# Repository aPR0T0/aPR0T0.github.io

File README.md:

# apr0t0.github.io

A minimal, terminal-driven personal site for **Mohd Alqama Shaikh** — robotics &
embedded systems engineer.

Text-based, squared, monospace. Visitors can navigate either way:

- **Click** the GUI nav / links, or
- **Type** commands in the terminal: `./about`, `./resume`, `./projects`, `./projects/rdog`,
  `./blogs`, `./blogs/<slug>`, `./publications`, `./contact`, plus `ls`, `help`,
  `theme`, `whoami`, `clear`.

There's also a hidden **mascot**: type `traxx` (or `./angry-dario`, or any
[PetDex](https://petdex.dev) pet like `./boba` / `petdex random`) to summon an
interactive character that roams the page — see [Mascots](#mascots-interactive-characters).

## Stack

Pure static — no production build step or package installation. The portfolio
uses classic scripts and also works from disk. Beam Lab uses ES modules and
browser storage, so serve that section over HTTP or HTTPS.

```
index.html    structure + styles (squary terminal shell, light/dark)
posts.js      blog posts data (window.BLOG_POSTS) — rewritten by the editor
content.js    page content: bio, projects, publications, contact
app.js        terminal engine + hash router + commands
author.js     password-gated blog editor (WebCrypto + GitHub commit)
traxx.js      interactive mascot engine (pluggable characters)
characters/   one folder per mascot: character.js config + .svg frames
petdex.js     local PetDex pet provider (reads window.PETS)
pets/         vendored PetDex spritesheets + generated manifest.js
scripts/      fetch-pets.mjs — download/refresh vendored pets
media/        curated project images
sem/          SEM project plan and current design map
sem/lab/      published Beam Lab simulator, guides, and local-edition download
Phased-arrays/ Phased Array Bench (self-contained page, vendored three.js r128)
vla/          VLA pipeline blog in 3D (self-contained page, vendored three.js r128)
```

## Phased Array Bench

[Phased Array Bench](https://apr0t0.github.io/Phased-arrays/) is where I visualize phased arrays and study how they work: an interactive AESA model with beam-pattern scopes, a 3D radiation pattern, an exploded 3D model of the antenna tile, a link budget, and a dependency graph. It is one self-contained page in the site theme (shared light/dark choice). three.js r128 and OrbitControls are vendored in `Phased-arrays/vendor/` so the 3D views don't depend on a CDN. The [blog post](https://apr0t0.github.io/#blogs/phased-arrays) links to it, and `node scripts/check-phased-arrays.mjs` checks the page, vendored hashes and links before deploy.

## VLA pipeline in 3D

[Vision-Language-Action models, end to end](https://apr0t0.github.io/vla/) is a long-form post on how a robot foundation model gets made (the π0 / OpenVLA / GR00T-style recipe). The article scrolls along a vertical line of eight stages while a sticky 3D view shows each one: the pipeline graph, VLM pretraining, ALOHA-style teleop data collection, an action expert doing flow matching, towel-fold post-training, parallel RL environments, sim vs. real evaluation, edge quantization, and a bimanual robot running the policy in its control loop. Pointing at a stage previews its scene and clicking jumps to it. `?scene=N&t=S` opens one scene frozen at time `S`.

Everything is procedural three.js (r128 + OrbitControls, vendored in `vla/vendor/`), drawn in the site palette with the shared light/dark choice. `engine.js` is the 3D kit (materials, arms with IK, labels), `robots.js` holds the rigs and scripted tasks, `scenes-*.js` are the nine scenes and `page.js` is the scroll / hover runtime. The [blog entry](https://apr0t0.github.io/#blogs/vla) links to it, and `node scripts/check-vla.mjs` checks the page, vendored hashes, scenes and links before deploy.

## microchooser

[microchooser](https://apr0t0.github.io/microchooser/) picks the cheapest, easiest microcontroller or dev board for the peripherals you need, with buy links and KiCad symbols and footprints. It is built and deployed from its own repository, [aPR0T0/microchooser](https://github.com/aPR0T0/microchooser), which GitHub Pages serves at `/microchooser/`. This site links to it from the navigation and the projects page, using absolute URLs so the local link checks don't look for a `microchooser/` folder here.

## Agent Remote

[Open Agent Remote](https://apr0t0.github.io/remote/) is a permanent start page for a private OpenCode/Codex workspace. It remembers a Tailscale relay address in the visitor's browser and opens that private relay directly. Authentication and agent traffic stay on the relay laptop.

The page also provides a clean Windows/macOS/Linux laptop kit with launchers and a local setup GUI. Viewing devices need Tailscale and a supported browser; laptops hosting agents also run the connector. The public files contain no personal relay key, pairing, provider login, or conversation data.

The [Agent Remote release post](https://apr0t0.github.io/#blogs/agent-remote-private-ai-workspace) uses the portfolio's normal blog layout and provides direct downloads:

- Android: [`remote/agent-remote-latest.apk`](https://apr0t0.github.io/remote/agent-remote-latest.apk)
- Laptop kit: [`remote/agent-remote-laptop.zip`](https://apr0t0.github.io/remote/agent-remote-laptop.zip)

Both stable links are updated together. `remote/release.json` records their matching version and hashes, and `remote/checksums.txt` includes both files. The post explains paused transfers, native Codex visibility, and the need to update every laptop connector.

Refresh from the Agent Remote source project:

```bash
npm run apk
npm run build:pages
npm run stage:pages -- /path/to/apr0t0.github.io
```

Run `node scripts/check-remote.mjs` in this repository before publishing. It checks the public asset hashes, download checksum, archive paths, launcher permissions, and navigation link.

## Run locally

Just open `index.html` in a browser — it works offline via `file://`.

Or serve it (nicer hash-route behavior):

```bash
python3 -m http.server 8000
# open http://localhost:8000
```

Hash routes are shareable (e.g. `#projects/rdog`). Deploys to GitHub Pages via
`.github/workflows/deploy.yml`, which checks simulator assets and blog links
before publishing the repo root.

## Beam Lab and build journal

- [Launch Beam Lab](https://apr0t0.github.io/sem/lab/)
- [Read the project journal](https://apr0t0.github.io/#blogs/building-a-simple-electron-microscope)
- [SEM project plan](https://apr0t0.github.io/sem/)

The hosted simulator runs entirely in the visitor's browser. BOM edits and
named setups stay in that browser's storage; they never rewrite this repository.
Component research needs the localhost edition and the visitor's own Codex
session. A curated, self-contained local source ZIP is linked from
`sem/lab/run-locally.html`; it requires no access to the private development repo.

The 512 × 512 butterfly preset uses 140 µm field width and about 109 minutes of
modeled hardware acquisition. The 500× preview takes about 13 seconds. Images
are synthetic; the electronics are unbuilt reference designs.

Refresh the hosted copy from the Beam Lab source checkout:

```sh
node /path/to/simplest-electron-microscope/simulator/build-static.mjs \
  --out /path/to/portfolio/sem/lab \
  --base-path /sem/lab/ \
  --blog-url '/#blogs/building-a-simple-electron-microscope'
node scripts/check-sem.mjs
```

The publisher uses an explicit asset list, records SHA-256 hashes, preserves
the base version, and omits personal run history, credentials, and development
data. Commit the refreshed `sem/lab/` files alongside any journal changes;
the Pages workflow does not need private-repository credentials.

## Editing content

Page content lives in `content.js`: bio, projects, publications, and contact
channels. Add a project by appending to the `projects` array; drop images into
`media/<id>/` and reference them in that project's `media` list. Blog posts live
in `posts.js` (`window.BLOG_POSTS`).

The `./resume` page is the `resume` object in `content.js`; its bullets are
inline markdown, so they can link to `#projects/<id>` / `#blogs/<slug>`. The
downloadable copy is `media/resume/alqama-shaikh-resume.pdf` — replace that file
when the resume changes.

## Mascots (interactive characters)

Type a character's name in the terminal to summon a little companion. It pops
out of the terminal, roams the screen, turns to watch the prompt while you type,
and panics when you pick it up and drag it anywhere.

```
traxx            summon / hide DJ TRAXX (the default)
traxx <name>     summon a specific character   (e.g. traxx angry-dario)
./<name>         same, in the site's ./ style  (e.g. ./angry-dario)
traxx list       list registered characters
traxx bye        send the current one away     (Esc or the × button work too)
```

`angry-dario` ships as a second, ready-to-copy example.

### PetDex pets (vendored locally)

`petdex.js` connects the same engine to pets from [PetDex](https://petdex.dev),
the gallery of animated Codex pets. Pets are **vendored into this repo** (their
spritesheets live under `pets/`), so they load from the site's own origin — no
runtime calls to petdex.dev. That makes them **blocker-proof, offline-proof, and
`file://`-friendly** (an earlier CDN-streaming version showed only a placeholder
when an ad/tracking blocker blocked the CDN — this fixes that for good).

```
./<slug>              summon an INSTALLED pet   (local, instant, offline)
<slug>                same, without the ./
spawn <name>          fetch ANY petdex pet by name over the network, then show it
petdex list           list installed pets
petdex find <query>   search installed pets
petdex random         summon a random installed pet
petdex state <id>     play any expression on the current pet (see below)
petdex seats on|off   perch the current pet on every nav / toolbar button
petdex bye            send it away              (Esc / × also work)
```

`./<slug>` only loads pets that are **vendored** in this repo (no network — works
offline / behind blockers). To bring in a pet that isn't installed yet, use
`spawn <name>`: it goes to petdex.dev, resolves the name, and loads the sprite on
demand (needs a connection, and won't work if petdex.dev is blocked). If you want
that pet to be permanent + offline, vendor it with the script below.

**Installing pets** — one command downloads them into `pets/` and regenerates
`pets/manifest.js`:

```bash
node scripts/fetch-pets.mjs boba dalek pixel-panda   # add pets by name/slug
node scripts/fetch-pets.mjs --curated                # add all official curated pets
node scripts/fetch-pets.mjs --remove homelander      # drop one
```

Names can be slugs, display names, or `petdex.dev/pets/<slug>` URLs. Browse the
gallery at [petdex.dev](https://petdex.dev) to find names. Commit the new files
in `pets/` and they deploy with the site. (Sheets are re-encoded for size; a full
sheet is ~0.5 MB.)

Each pet is one spritesheet whose rows are the **9 animation states**, all
reachable (`petdex state <id>`): `idle`, `running-right`, `running-left`,
`waving`, `jumping`, `failed`, `waiting`, `running`, `review`. The engine maps
them to behaviour automatically — it runs left/right while roaming, `review`s
while you type, and `failed`s (panics) when you grab it. Every so often the
roaming pet **walks over and hops onto a button**, sits *on top* of it, comments
on that option, then **hops from button to button** before dropping back down —
no command needed. You can also **drag the pet onto any button** to seat it there
yourself. All of this works for whichever character is out (`./boba`, `./nukey`,
`spawn <name>`, …), not just one.

`petdex seats on` perches a pet on **every nav / toolbar button**. They *rain in*
(each drops onto its button with a bounce), then keep it lively — every few
seconds a random one **falls onto its button again** or pops a little speech
bubble riffing on that option (e.g. on `./projects`: "ooh, robots!"; on the theme
button: "flip the lights!"). Hovering a button makes its pet **wave** and comment;
clicking makes it **jump**; the current page's pet sits in `review`. Use
`petdex seats <name>` to pick who sits, `petdex seats off` to clear. If a sheet is
ever missing, the pet shows a labelled placeholder instead of an invisible walker.

Pets are community fan art — code is MIT, assets belong to their submitters
([takedowns](https://github.com/crafter-station/petdex)).

### Add your own

A character is just a folder under `characters/` plus a one-line script tag — no
build step.

1. Create `characters/<id>/` and add SVG frames (any `viewBox`, drawn facing the
   viewer). Only `idle.svg` is required; the rest fall back to it:

   ```
   characters/my-bot/
     idle.svg     required — resting pose
     look.svg     optional — shown while you type
     panic.svg    optional — shown while held / dragged
   ```

2. Add `characters/my-bot/character.js`:

   ```js
   window.Traxx.define({
     id: "my-bot",
     name: "MY BOT",
     height: 140, aspect: 112/140, speed: 64,
     sign: { bg: "#111", fg: "#0af" },      // LED name-tag (or null to hide)
     states: {
       idle:  { frames: "idle",  anim: "bob-slow" },
       walk:  { frames: "idle",  anim: "bob" },
       look:  { frames: "look",  anim: "bob-slow", lean: true },
       panic: { frames: "panic", anim: "shake" },
     },
     speech: {
       hello: ["hi!"], panic: ["aaah!"], land: ["oof."], idle: ["..."],
     },
   });
   ```

3. Load it in `index.html`, after `traxx.js`:

   ```html
   <script src="./characters/my-bot/character.js"></script>
   ```

   Then run `./my-bot`.

**Notes**

- `frames` is an SVG name (without `.svg`), or a list to cycle for frame-by-frame
  animation — `{ frames: ["walk-a","walk-b"], fps: 8 }`.
- `anim` is a built-in motion — `bob-slow`, `bob`, `shake`, `none` — or a custom
  one you supply via a `css` field (see `characters/angry-dario` for a `stomp`
  example). `lean: true` makes the character tilt toward the prompt.
- Frames are plain `` loads, so mascots work offline over `file://` too.
- Respects `prefers-reduced-motion`, is touch-friendly, and only one mascot is
  out at a time.

## Author mode (in-browser blog editor)

Blog posts can be written/edited from the terminal and committed straight to the
repo — no backend. Your GitHub token is encrypted with a password using real
WebCrypto, so no secret is ever stored in plaintext.

**Crypto:** AES-256-GCM with a key derived via PBKDF2-SHA256 (600,000
iterations, random 16-byte salt + 12-byte IV). `login` decrypts the token with
your password; a wrong password fails AES-GCM auth-tag verification, so the
password *is* the key (no separate hash is kept).

**Commands:**

```
auth setup      encrypt a GitHub token with a password (one time)
login           unlock author mode with your password
edit <slug>     edit a post in an inline editor, then commit
new             write a new post, then commit
auth publish    store the encrypted blob in the repo (auth.json) for
                cross-device login — it stays ciphertext, never plaintext
auth status     show current auth state
auth reset      remove the encrypted blob from this browser
logout          lock author mode
```

Committing rewrites `posts.js` via the GitHub Contents API; GitHub Pages then
redeploys automatically (~1 min).

**Security notes**

- Use a **long passphrase**. The encrypted blob (in `localStorage`, or in
  `auth.json` if you publish it) is only as safe as your password is hard to
  brute-force.
- Use a **fine-grained personal access token** scoped to **only this repo** with
  **Contents: read & write** and an **expiry**. That caps the blast radius.
- Requires a secure context (https or localhost / `file://`) for WebCrypto.

## RK3566 circuit simulation lab

[Open the RK3566 lab](https://apr0t0.github.io/rk3566/) to explore the Revision 4
PCB, saved simulation runs, model studies, and electromagnetic field analysis.
The site navigation and `./projects/rk3566` also link to the lab.

The Pages package is a dated snapshot of the local analysis. Interactive views,
playback, saved-run selection, and evidence downloads work on Pages. New Python
solver runs and validation sweeps require the local simulation service.
`rk3566/publication.json` records the export time, source identities, API-to-file
mapping, and hashes of the exported evidence. See `scripts/export-rk3566.py` for
the repeatable data export and `rk3566/README.md` for the published UI behavior.

Validate with `node scripts/check-rk3566.mjs`; the Pages workflow runs this check
alongside the existing SEM and Agent Remote checks before deploying.

The [whole-board magnetic view](https://apr0t0.github.io/rk3566/#magnetic) adds
conditional contributions from the saved averaged power-rail currents across the
55 × 55 mm board. It supports height selection, B/H field values, source selection,
playback and probes; the same study is available in the 3D workbench. Each current
path and return is an explicit geometric assumption. Unsupported current paths
remain outside the modeled sum and are listed in its coverage report.

Generate its evidence with `python3 -B board_magnetic.py` from the local simulation
directory before running the Pages export. `node scripts/check-board-magnetic.mjs`
checks the published field data and its numerical contract.

## robot-learning node map

[robot-learning](https://apr0t0.github.io/robot-learning/) is the code that goes with the VLA post: a node-based pipeline where every stage has a working base and every paper is a swappable component, configured from YAML or Python. The page in `robot-learning/` is a node map of that repo (stages, components with their params and papers, pipeline DAGs, and the files that implement each one). It is generated in the robot-learning repo by `scripts/build_site.py` and copied here with its `scripts/publish_site.sh`; `node scripts/check-robot-learning.mjs` checks the page, its graph data and the links before deploy.

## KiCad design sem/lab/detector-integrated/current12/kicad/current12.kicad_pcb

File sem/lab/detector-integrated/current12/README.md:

# Specimen-current board · current12

Current12 · B0 · unbuilt. One DC input powers the existing LMC662 / ADS1115 measurement circuit. Connect the insulated conductive specimen holder to SUM. The amplifier common and chamber share one deliberate ground reference.

Input: 12 / 24 V · regulated 9–30 V. Local rails: ±5 V analog · 3.3 V ADC.

## Exact external connections

Connector pin numbers, not screen orientation, define the wiring. Pin 1 uses the marked / square pad in the native footprint. Match this revision before assembly.

| Pin | Net | External connection | Detail |
|---|---|---|---|
| J2.1 | VIN | DC source +12 V or +24 V | Use regulated 9–30 V; verify polarity before applying power. |
| J2.2 | PGND | DC source negative | Primary return; bonded to local analog ground on this board. |
| J1.1 | SUM | Insulated conductive specimen holder | Feedthrough centre only. No second ground connection to the specimen holder. |
| J1.2 | AGND | Input guard / shield | Grounded-reference guard. Keep the signal conductor insulated from it. |
| J3.1 | AGND | ESP32 GND | Reference for the direct I²C signals. |
| J3.2 | +3V3 | Leave open | ADC reference OUTPUT; do not feed or power an ESP32 through this pin. |
| J3.3 | SDA | ESP32 GPIO21 | 3.3 V I²C data. Both devices must be powered while connected; coordinate power or disconnect before separate power cycling. |
| J3.4 | SCL | ESP32 GPIO22 | 3.3 V I²C clock. |
| J3.5 | RDY | Leave open with the supplied polling sketch | Optional ADC conversion-ready output. |
| J4.1 | PGND | Chamber / enclosure ground star | Use a separate mechanically secure protective-earth bond for accessible metal; PCB wiring is not that bond. |
| J4.2 | PGND | Same ground star / shield return | Duplicate PGND terminal; internally connected to J4.1. |

## Design files

- Open `kicad/current12.kicad_pro` with KiCad 10. The complete design ZIP includes all hierarchical sheets and local libraries.
- `exports/schematic.pdf` contains every schematic sheet.
- `exports/assembly.svg` identifies the component positions.
- `bom.csv` contains the selected parts; prices are not quoted.
- `verification/check-summary.json` records native checks and checked-file hashes.
- `fabrication.zip` contains prototype manufacturing outputs. Inspection and bench commissioning remain required.

Use the original ESP32_LMC662_scan sketch and DAC80502 scan board. J3.2 is the ADC reference **output**, which remains open with that host. Read the separate scan-board connection guide.

---

## Shared architecture and commissioning

Two unbuilt PCB prototypes extend the original LMC662 / ADS1115 detector. Use the [interactive board and pin guide](https://apr0t0.github.io/sem/lab/power.html) to select specimen current or the positive collector. Both accept a regulated 9–30 V input, including nominal 12 V and 24 V. This supply powers detector electronics and collector bias; the electron gun, scan drivers and grounded ESP32 have separate supplies.

## What is onboard

Input fuse and reverse-polarity diode → LMR51420 500 kHz buck → approximately 5.09 V → RECOM R05P09D/P isolated raw ±9 V → RC filtering → TPS7A49 / TPS7A30 local ±5 V. The ADC runs from its own 3.3 V supply regulator. The collector also has a separate digital 3.3 V rail, an ATmega328P and two VO2611-X016 optocouplers.

The collector's XP Power CA02P-5 module is soldered onto the same board. It creates programmable 0–200 V from the onboard 5 V bus. Two 10 kΩ filter stages and 100 nF / 1 µF capacitors feed FCOM. Nominal FCOM at a raw 200 V is about 199.6 V because of bleeder loading. A TPS2553-1 latch-off switch limits the bias-module input: 88.7 kΩ / 1% programs a calculated 262–342 mA range, below the module’s 420 mA short-protection input limit. Its active-LOW fault goes through J3.7 to ESP32 GPIO34. Verify startup and current-limit behavior on the assembled board. Program linearity is specified from 15% of full scale, so treat low-bias settings as requiring calibration.

The isolated supply and HV converter are packaged modules; the buck is a discrete IC / inductor circuit. This is a self-contained onboard power design, not an entirely discrete magnetics design. Obtain current distributor quotes: the HV module may dominate cost.

Both layouts use local top/bottom PGND copper and six stitching vias around the buck's ground returns. The amplifier's C9/C10 bypass capacitors have direct 0.75 mm returns to the quiet AGND or FCOM plane. The guarded SUM trace and its no-plane region remain separate. These filled-copper connections were inspected in the native boards; their noise performance still requires measurement.

## Choose the current path

| Connection | Specimen-current board | Collector board |
|---|---|---|
| J1.1 SUM | Insulated conductive specimen holder | Separate insulated metal collector |
| J1.2 guard | AGND, near chamber ground | FCOM, near positive collector bias |
| Specimen | Only through SUM; insulated from stage | Grounded conductive contact |
| Local analog common | Deliberately bonded to PGND/chamber | Elevated FCOM |
| J3 data | Direct 3.3 V I²C to ESP32 | Ground-side UART through two optocouplers |
| Extra bias | None | Generated and filtered onboard |

The specimen-current board’s direct I²C is not isolated during power-off. Keep both host and detector powered while connected, using coordinated power; disconnect the interface before separately power-cycling either side. The collector uses host-powered VIO at J3.2 for its ground-side UART interface.

SUM is the amplifier input. The positive bias connects to FCOM, never directly to SUM; a direct bias wire would bypass the measurement. At steady state, unsaturated feedback holds SUM close to the amplifier's local common. The collector reading is net collected electron current, potentially a mixture of SE, BSE and background. There is no charge multiplication on a plain metal collector. An insulating specimen still needs a charging solution.

## Collector boundary

The complete analog circuit, ADS1115 and ATmega328P operate relative to FCOM. The primary side, CA converter case/return, outer enclosure, accessible cable shield, grounded specimen and scan ESP32 operate relative to chamber ground. Only the rated isolated converter, two optocouplers and deliberate filtered bias network bridge these references. No grounded USB, programming or oscilloscope cable belongs on FCOM while biased.

Mount the collector PCB on nylon / PEEK standoffs with insulating fasteners. Four 3.2 mm holes reserve a maximum 6.4 mm diameter insulating washer envelope. A grounded screw head is not an electrically neutral hole: maintain separation from grounded metal above and below the floating copper.

The PCB design enforces a 5 mm copper separation between primary and FCOM regions and a separate 2 mm rule between grounded-side HV and low-voltage conductors. These are layout rules, not certification. RECOM's 250 VAC rms basic working insulation is the relevant published working specification; 6.4 kV is a brief test rating. Converter and optocoupler capacitance still carries displacement current. Rail filters cannot remove every path for common-mode pickup.

## Collector startup and shutdown

1. Verify component orientations, cleanliness, connector numbering and the exact BOM. Assemble and inspect the input power stages before fitting the high-impedance parts where practical.
2. With the electron beam blanked and the HV module disabled, power from a current-limited regulated source. Verify 5 V bus, ±9 V raw rails, ±5 V local rails and both 3.3 V domains using their correct reference. Repeat at 12 V and 24 V and across expected loads.
3. Program the ATmega328P for an external 8 MHz crystal and 3.3 V operation with bias disabled and verified discharged. Remove all ICSP connections. Connect the grounded ESP32 via the specified UART, two control pins and active-LOW fault input. Feed collector J3.2 HOST_VIO from the ESP32’s 3.3 V rail (allow 19 mA); this removes the board-powered LED/pull-up injection path into host GPIO. Leakage and hot-plug behavior remain unverified. On the specimen-current board, J3.2 is instead a reference output and is left open.
4. Begin with the bias pot at minimum. The ESP32 first confirms the optical link. Its `b` command raises HV_ENABLE while holding PGM_RELEASE LOW for at least 100 ms, then releases the buffered RC ramp. Hardware also uses a TPS3808G50 to qualify the actual module 5 V rail, with a datasheet delay of 180–420 ms before allowing PGM_RELEASE to release the clamp. The buffer remains powered from the unswitched 5 V bus. A 10 kΩ / 47 µF command filter gives about 0.47–0.59 s nominal ramp time; effective capacitance and leakage must be checked. The sketch keeps the beam blanked for a 10 s initial settling policy and checks the optical link during that interval. That delay is a starting policy, not a guarantee of pA settling. Measure the actual bias rise, overshoot and settling before deciding the interval is adequate.
5. With bias steady and beam blanked, use `z` to measure a new zero. Only then use `s` for a scan. Repeat zero after any bias adjustment. The acquisition sequence requests fresh ADC conversions; CRC, request IDs, status and timeouts reject incomplete or stale replies.
6. `x` aborts, blanks the beam, clamps programming to zero and removes the CA module's 5 V input. Passive bleeders remain connected. Check voltage with a rated instrument before touching or attaching a programmer; a software OFF state is not proof of discharge.

The final 1 µF capacitor alone stores 20 mJ at 200 V. Its independent 9.98 MΩ bleeder has a 9.98 s time constant, but additional paths and unspecified module internal capacitance affect whole-assembly discharge. Measure the complete assembly, including cables and relevant faults. These software controls are not a certified beam interlock.

## Proving that readings are electrons

- Inject a known local current into SUM at zero bias and elevated bias. Establish gain, sign, offset, clipping and settling with the real cable and feedthrough.
- Log the collector dark current with pumps, heater, converters and UART operating. Repeat a raster with the beam blanked and then blocked upstream; image structure under those conditions is pickup.
- Compare repeated scans and measured incident beam current. Repeat at fixed, settled bias values. Separate bias-dependent leakage and displacement current from collection changes.
- Record raw ADC codes, zero, calibration, timing, measured bias and all faults. A clean DRC does not establish a picoampere noise floor.

The board-specific package contains the exact connector schedule, native CAD, BOM, CAD results and prototype fabrication outputs. The original externally powered Rev A and the earlier battery / fibre collector concept remain separate options on their original pages.

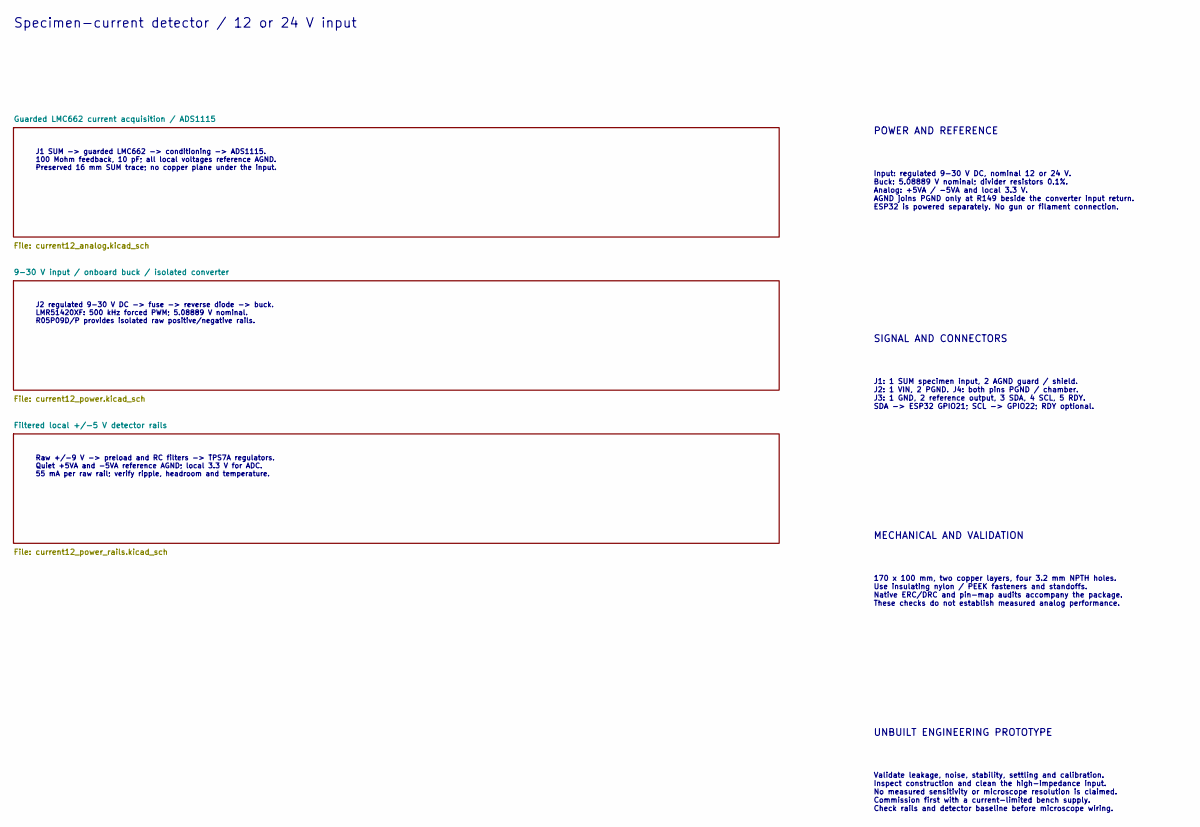
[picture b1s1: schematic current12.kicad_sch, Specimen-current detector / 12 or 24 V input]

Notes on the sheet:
Specimen-current detector / 12 or 24 V input
J1 SUM -> guarded LMC662 -> conditioning -> ADS1115. 100 Mohm feedback, 10 pF; all local voltages reference AGND. Preserved 16 mm SUM trace; no copper plane under the input.
J2 regulated 9-30 V DC -> fuse -> reverse diode -> buck. LMR51420XF: 500 kHz forced PWM; 5.08889 V nominal. R05P09D/P provides isolated raw positive/negative rails.
Raw +/-9 V -> preload and RC filters -> TPS7A regulators. Quiet +5VA and -5VA reference AGND; local 3.3 V for ADC. 55 mA per raw rail; verify ripple, headroom and temperature.
POWER AND REFERENCE
Input: regulated 9-30 V DC, nominal 12 or 24 V. Buck: 5.08889 V nominal; divider resistors 0.1%. Analog: +5VA / -5VA and local 3.3 V. AGND joins PGND only at R149 beside the converter input return. ESP32 is powered separately. No gun or filament connection.
SIGNAL AND CONNECTORS
J1: 1 SUM specimen input, 2 AGND guard / shield. J2: 1 VIN, 2 PGND. J4: both pins PGND / chamber. J3: 1 GND, 2 reference output, 3 SDA, 4 SCL, 5 RDY. SDA -> ESP32 GPIO21; SCL -> GPIO22; RDY optional.
MECHANICAL AND VALIDATION
170 x 100 mm, two copper layers, four 3.2 mm NPTH holes. Use insulating nylon / PEEK fasteners and standoffs. Native ERC/DRC and pin-map audits accompany the package. These checks do not establish measured analog performance.
UNBUILT ENGINEERING PROTOTYPE
Validate leakage, noise, stability, settling and calibration. Inspect construction and clean the high-impedance input. No measured sensitivity or microscope resolution is claimed. Commission first with a current-limited bench supply. Check rails and detector baseline before microscope wiring.

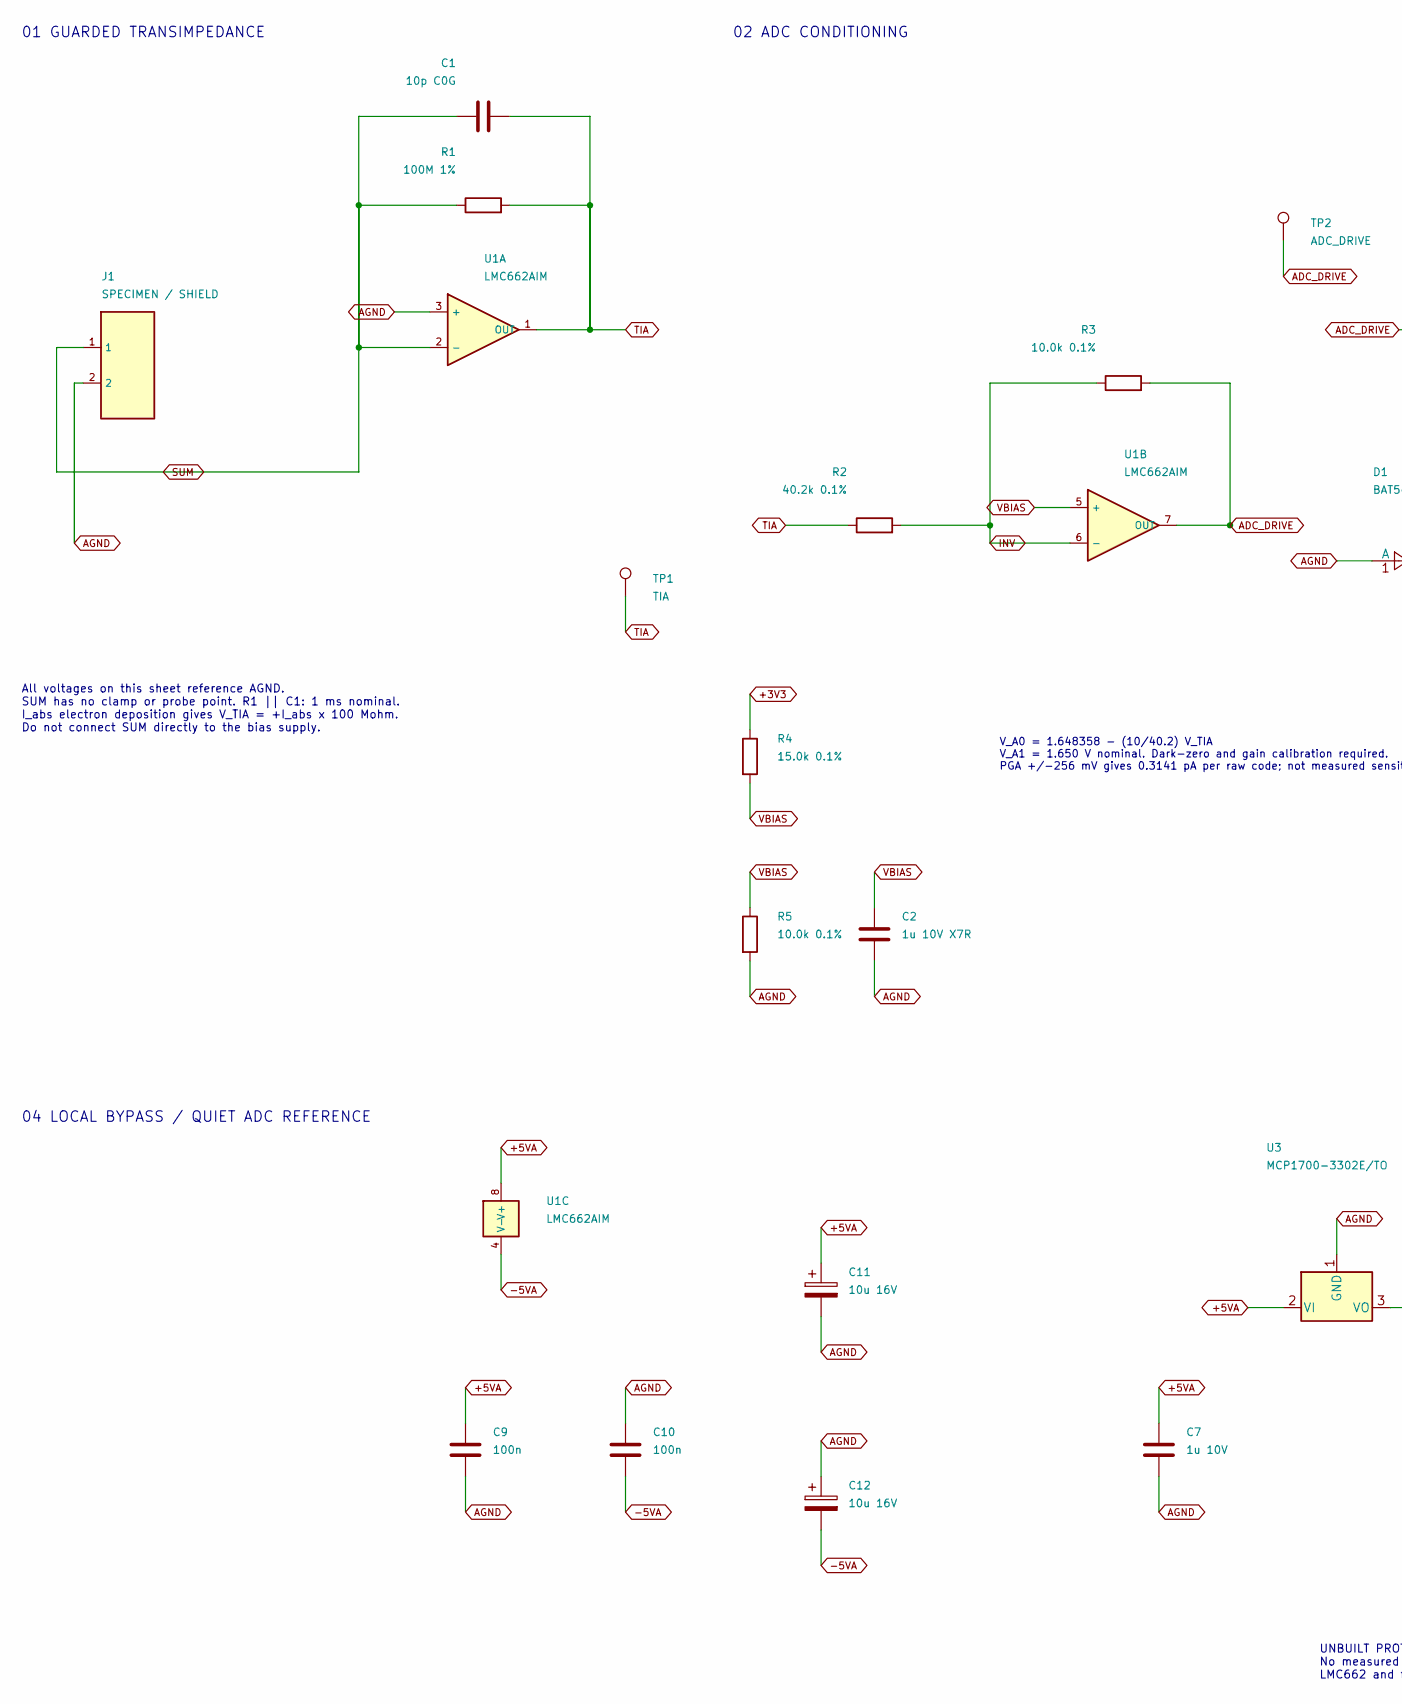
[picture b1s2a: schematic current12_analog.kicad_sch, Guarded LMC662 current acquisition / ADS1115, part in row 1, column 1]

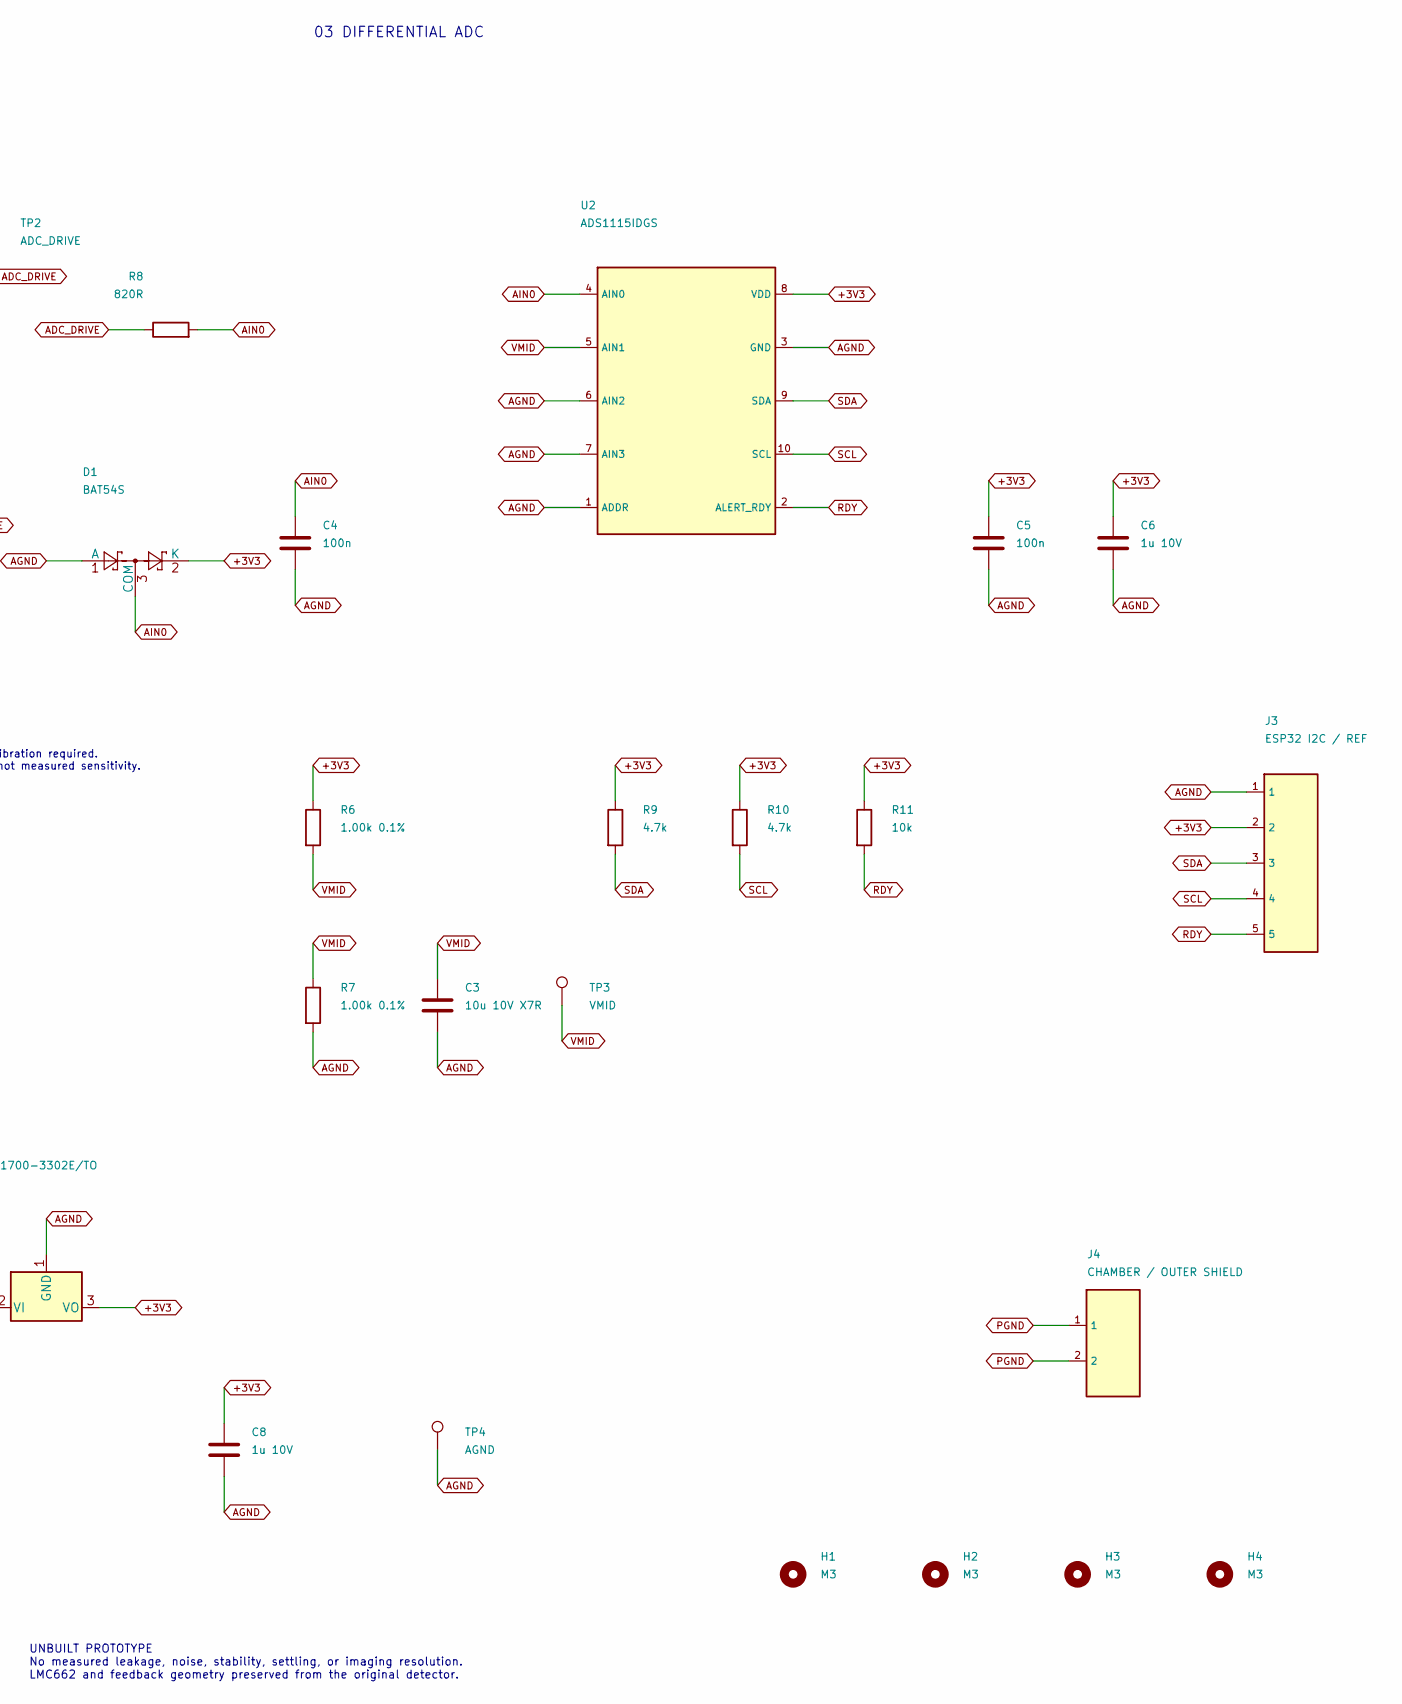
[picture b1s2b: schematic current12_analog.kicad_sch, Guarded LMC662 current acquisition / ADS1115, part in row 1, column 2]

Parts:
C1: 10p C0G; C_Disc_D3.0mm_W1.6mm_P2.50mm
C2: 1u 10V X7R; C_0805_2012Metric
C3: 10u 10V X7R; C_0805_2012Metric
C4, C5, C9, C10: 100n; C_0805_2012Metric
C6, C7, C8: 1u 10V; C_0805_2012Metric
C11, C12: 10u 16V; CP_Radial_D5.0mm_P2.00mm
D1: BAT54S; SOT-23; MPN BAT54S
H1, H2, H3, H4: M3; MountingHole_3.2mm_M3
J1: SPECIMEN / SHIELD; PinHeader_1x02_P2.54mm_Vertical
J3: ESP32 I2C / REF; PinHeader_1x05_P2.54mm_Vertical
J4: CHAMBER / OUTER SHIELD; PinHeader_1x02_P2.54mm_Vertical
R1: 100M 1%; R_Axial_DIN0207_L6.3mm_D2.5mm_P7.62mm_Horizontal; MPN HVA05FA100M
R2: 40.2k 0.1%; R_0805_2012Metric
R3, R5: 10.0k 0.1%; R_0805_2012Metric
R4: 15.0k 0.1%; R_0805_2012Metric
R6, R7: 1.00k 0.1%; R_0805_2012Metric
R8: 820R; R_0805_2012Metric
R9, R10: 4.7k; R_0805_2012Metric
R11: 10k; R_0805_2012Metric
TP1: TIA; TestPoint_THTPad_D2.0mm_Drill1.0mm
TP2: ADC_DRIVE; TestPoint_THTPad_D2.0mm_Drill1.0mm
TP3: VMID; TestPoint_THTPad_D2.0mm_Drill1.0mm
TP4: AGND; TestPoint_THTPad_D2.0mm_Drill1.0mm
U1: LMC662AIM; SOIC-8_3.9x4.9mm_P1.27mm; MPN LMC662AIMX/NOPB
U2: ADS1115IDGS; TSSOP-10_3x3mm_P0.5mm; MPN ADS1115IDGSR
U3: MCP1700-3302E/TO; TO-92_Inline; MPN MCP1700-3302E/TO

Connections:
+3V3: C5.1, C6.1, C8.1, D1.2 (K), J3.2, R4.1, R6.1, R9.1, R10.1, R11.1, U2.8 (VDD), U3.3 (VO)
+5VA: C7.1, C9.1, C11.1, U1.8 (V+), U3.2 (VI); also elsewhere on the board
-5VA: C10.2, C12.2, U1.4 (V-); also elsewhere on the board
ADC_DRIVE: R3.2, R8.1, TP2.1, U1.7 (OUT)
AGND: C2.2, C3.2, C4.2, C5.2, C6.2, C7.2, C8.2, C9.2, C10.1, C11.2, C12.1, D1.1 (A), J1.2, J3.1, R5.2, R7.2, TP4.1, U1.3 (+), U2.1 (ADDR), U2.3 (GND), U2.6 (AIN2), U2.7 (AIN3), U3.1 (GND); also elsewhere on the board
AIN0: C4.1, D1.3 (COM), R8.2, U2.4 (AIN0)
INV: R2.2, R3.1, U1.6 (-)
PGND: J4.1, J4.2; also elsewhere on the board
RDY: J3.5, R11.2, U2.2 (ALERT_RDY)
SCL: J3.4, R10.2, U2.10 (SCL)
SDA: J3.3, R9.2, U2.9 (SDA)
SUM: C1.1, J1.1, R1.1, U1.2 (-)
TIA: C1.2, R1.2, R2.1, TP1.1, U1.1 (OUT)
VBIAS: C2.1, R4.2, R5.1, U1.5 (+)
VMID: C3.1, R6.2, R7.1, TP3.1, U2.5 (AIN1)

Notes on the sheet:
01 GUARDED TRANSIMPEDANCE
02 ADC CONDITIONING
03 DIFFERENTIAL ADC
All voltages on this sheet reference AGND. SUM has no clamp or probe point. R1 || C1: 1 ms nominal. I_abs electron deposition gives V_TIA = +I_abs x 100 Mohm. Do not connect SUM directly to the bias supply.
V_A0 = 1.648358 - (10/40.2) V_TIA V_A1 = 1.650 V nominal. Dark-zero and gain calibration required. PGA +/-256 mV gives 0.3141 pA per raw code; not measured sensitivity.
04 LOCAL BYPASS / QUIET ADC REFERENCE
UNBUILT PROTOTYPE No measured leakage, noise, stability, settling, or imaging resolution. LMC662 and feedback geometry preserved from the original detector.

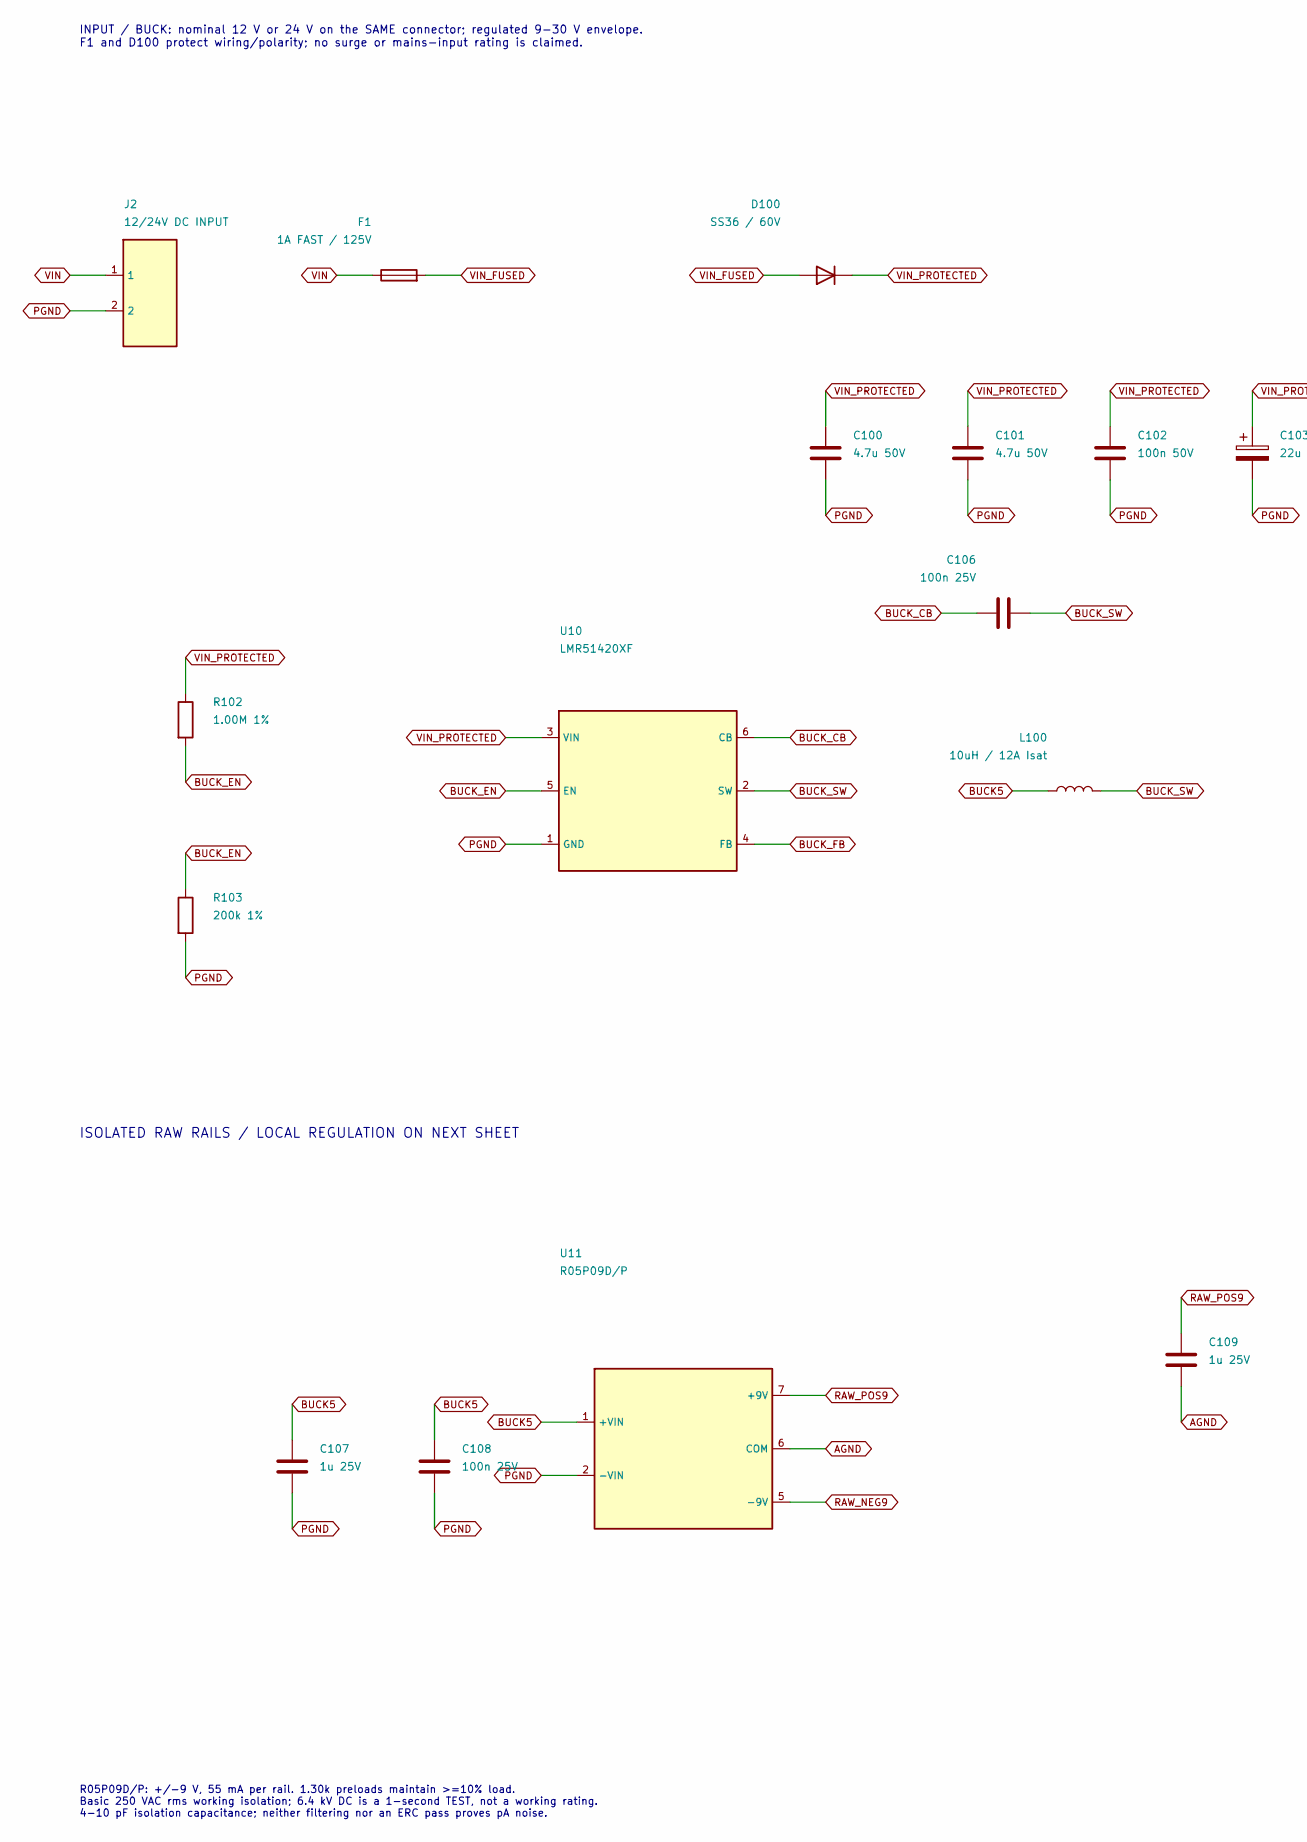
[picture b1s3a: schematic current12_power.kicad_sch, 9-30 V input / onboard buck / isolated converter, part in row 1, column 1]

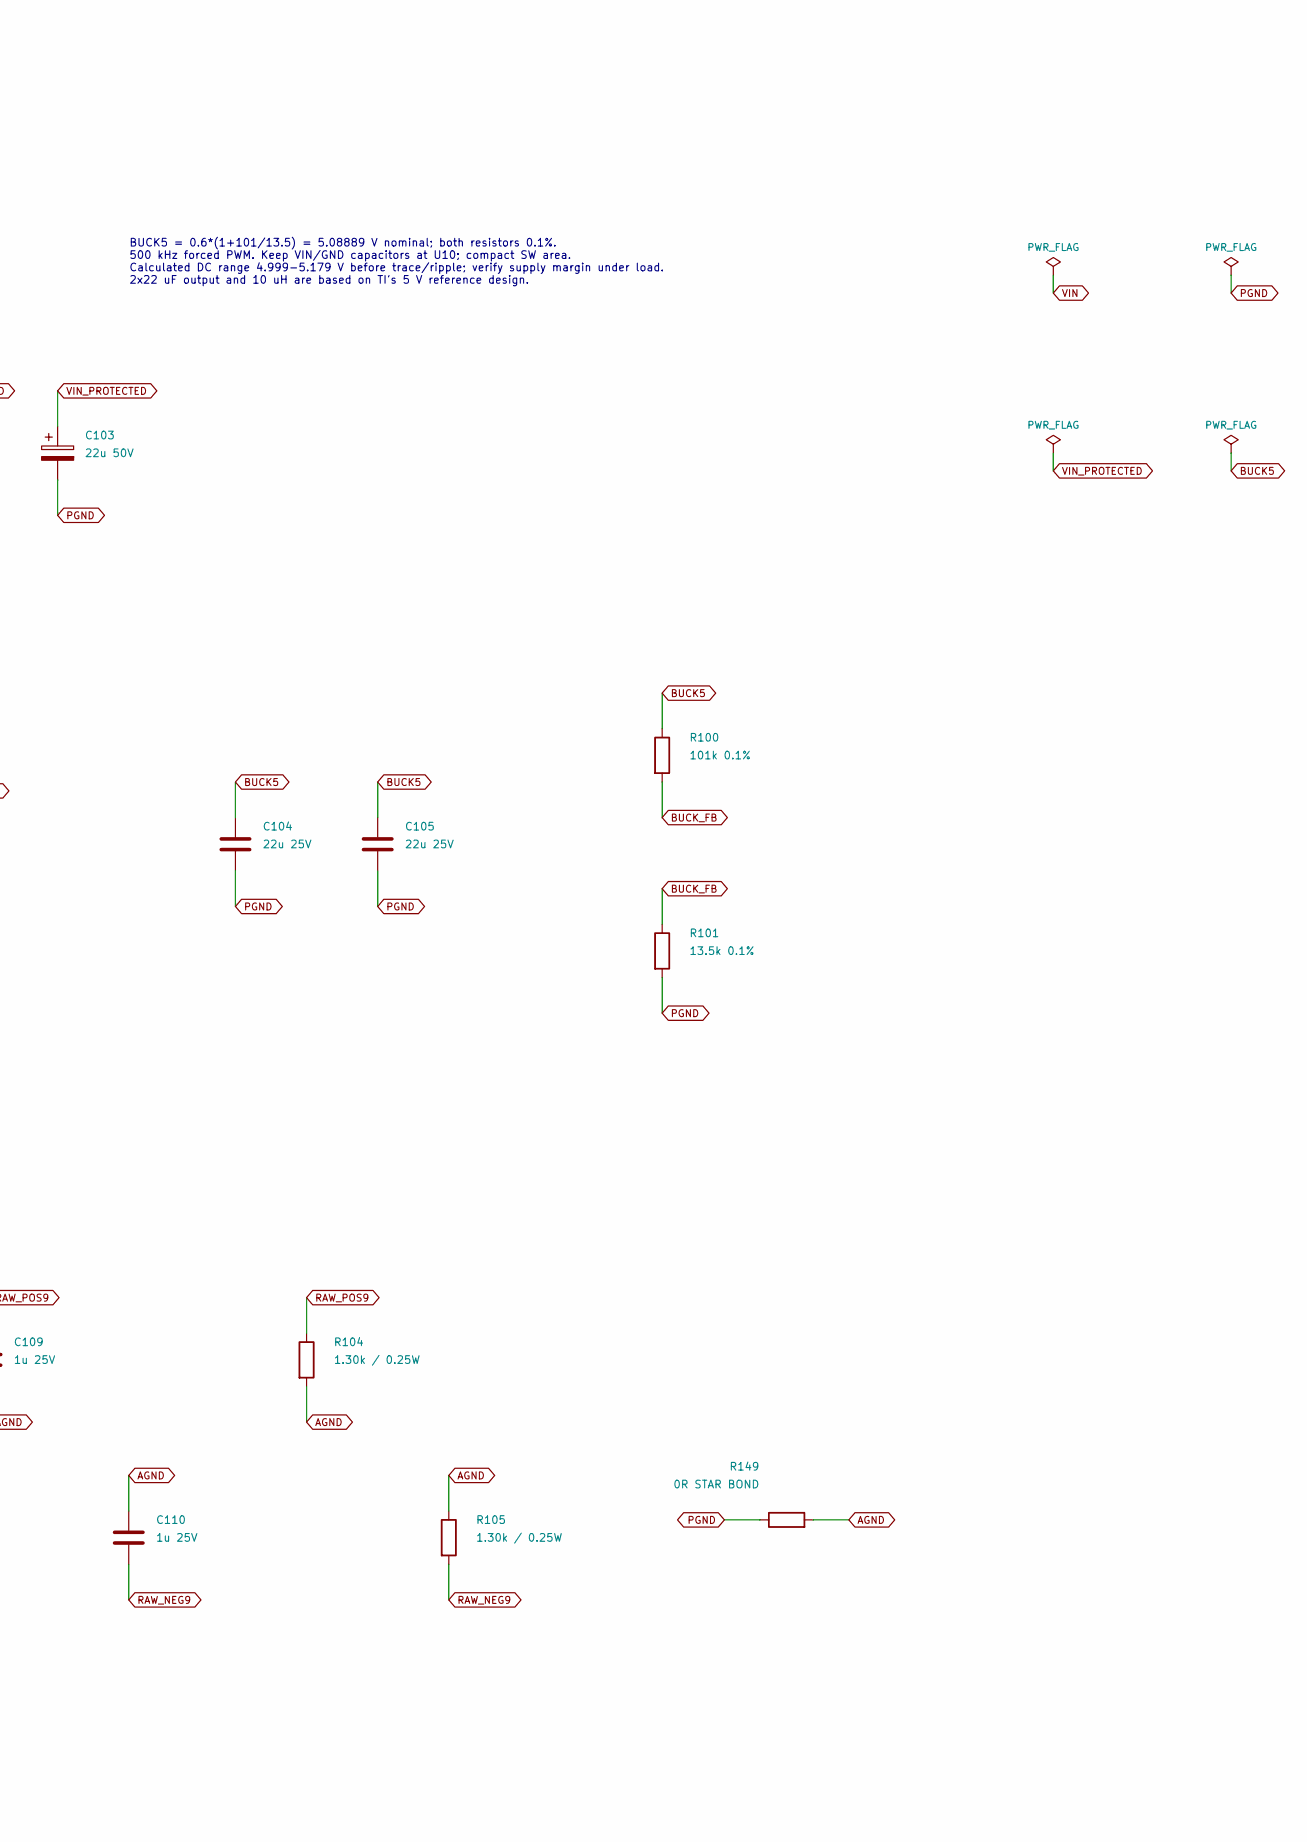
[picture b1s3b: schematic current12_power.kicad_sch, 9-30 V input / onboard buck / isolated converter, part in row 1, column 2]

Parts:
C100, C101: 4.7u 50V; C_1210_3225Metric
C102: 100n 50V; C_0805_2012Metric
C103: 22u 50V; CP_Radial_D8.0mm_P3.50mm
C104, C105: 22u 25V; C_1210_3225Metric
C106, C108: 100n 25V; C_0805_2012Metric
C107, C109, C110: 1u 25V; C_0805_2012Metric
D100: SS36 / 60V; D_SMC; MPN SS36-E3/57T
F1: 1A FAST / 125V; Fuse_Littelfuse-NANO2-451_453; MPN 0451001.MRL
J2: 12/24V DC INPUT; PinHeader_1x02_P2.54mm_Vertical
L100: 10uH / 12A Isat; Bourns_SRP1038A; MPN SRP1038A-100M
R100: 101k 0.1%; R_0805_2012Metric
R101: 13.5k 0.1%; R_0805_2012Metric
R102: 1.00M 1%; R_0805_2012Metric
R103: 200k 1%; R_0805_2012Metric
R104, R105: 1.30k / 0.25W; R_1206_3216Metric
R149: 0R STAR BOND; R_1206_3216Metric
U10: LMR51420XF; SOT-23-6; MPN LMR51420XFDDCR
U11: R05P09D/P; R05P09D_SIP7; MPN R05P09D/P

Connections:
AGND: C109.2, C110.1, R104.2, R105.1, R149.2, U11.6 (COM); also elsewhere on the board
BUCK5: C104.1, C105.1, C107.1, C108.1, L100.1, R100.1, U11.1 (+VIN)
BUCK_CB: C106.1, U10.6 (CB)
BUCK_EN: R102.2, R103.1, U10.5 (EN)
BUCK_FB: R100.2, R101.1, U10.4 (FB)
BUCK_SW: C106.2, L100.2, U10.2 (SW)
PGND: C100.2, C101.2, C102.2, C103.2, C104.2, C105.2, C107.2, C108.2, J2.2, R101.2, R103.2, R149.1, U10.1 (GND), U11.2 (-VIN); also elsewhere on the board
RAW_NEG9: C110.2, R105.2, U11.5 (-9V); also elsewhere on the board
RAW_POS9: C109.1, R104.1, U11.7 (+9V); also elsewhere on the board
VIN: F1.1, J2.1
VIN_FUSED: D100.2 (A), F1.2
VIN_PROTECTED: C100.1, C101.1, C102.1, C103.1, D100.1 (K), R102.1, U10.3 (VIN)

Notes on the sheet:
INPUT / BUCK: nominal 12 V or 24 V on the SAME connector; regulated 9-30 V envelope. F1 and D100 protect wiring/polarity; no surge or mains-input rating is claimed.
BUCK5 = 0.6*(1+101/13.5) = 5.08889 V nominal; both resistors 0.1%. 500 kHz forced PWM. Keep VIN/GND capacitors at U10; compact SW area. Calculated DC range 4.999-5.179 V before trace/ripple; verify supply margin under load. 2x22 uF output and 10 uH are based on TI's 5 V reference design.
ISOLATED RAW RAILS / LOCAL REGULATION ON NEXT SHEET
R05P09D/P: +/-9 V, 55 mA per rail. 1.30k preloads maintain >=10% load. Basic 250 VAC rms working isolation; 6.4 kV DC is a 1-second TEST, not a working rating. 4-10 pF isolation capacitance; neither filtering nor an ERC pass proves pA noise.
